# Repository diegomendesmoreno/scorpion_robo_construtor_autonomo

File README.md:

Scorpion, o Robô construtor autônomo
==============
Projeto de um Robô Construtor Autônomo, como o trabalho de conclusão de curso de Engenharia Eletrônica de 2015.

Time
--------------
- Allan Dinato Martins
- André Ferro Kopelingh
- Diego Mendes Moreno

Links
--------------
- [Blog - Scorpion, o Robô construtor autônomo](http://engenoob.blogspot.com.br/2015/06/scorpion-robo-construtor-autonomo.html)
- [YouTube - Scorpion, o Robô construtor autônomo](https://youtu.be/ymfdhoq2V6s)

Transcrição do código Arduino scorpion_robo_construtor_autonomo.ino
--------------

```c
/* Nome   : scorpion_robo_construtor_autonomo
 * Alunos : Allan Dinato Martins
 *          Andre Ferro Kopelingh
 *          Diego Mendes Moreno
 */

/* Includes */
#include <Stepper.h>
#include <Ultrasonic.h>
#include <Servo.h>

/* Pinos */
//Steppers
#define D1           22   //azul
#define D2           24   //rosa
#define D3           26   //amarelo
#define D4           28   //laranja
#define E1           30   //azul
#define E2           32   //rosa
#define E3           34   //amarelo
#define E4           36   //laranja
//Servos
#define serv_base_1  50   //servo da base direito
#define serv_base_2  52   //servo da base esquerdo
#define serv_brac_1  51   //servo do braço direito
#define serv_brac_2  53   //servo do braço esquerdo
#define serv_garra   8    //servo da garra
//Sensores Ultrasom
///Ultra 10
#define echoPin_f    48
#define trigPin_f    49
///Ultra 4
#define echoPin_fc   35
#define trigPin_fc   37
///Ultra 9
#define echoPin_d1   46
#define trigPin_d1   47
///Ultra 8
#define echoPin_d2   44
#define trigPin_d2   45
///Ultra 7
#define echoPin_e1   42
#define trigPin_e1   43
///Ultra 6
#define echoPin_e2   40
#define trigPin_e2   41
///Ultra 5
#define echoPin_t    38
#define trigPin_t    39

/* Defines */
//Constantes
#define ATRASO         2
#define OFFSET_LATERAL 0.2
#define OFFSET_AJUSTE  0.5
#define DIVISOR_ARRUM  0.04
#define CNT_MAPA_MAX   4000

/* Subrotinas */
//Sensores Ultrasom
void leitura_sensores(void);
void ultrasom(void);
void ultra_valores(void);
void limpa_media(void);
//Steppers
void frente(float passos);
void tras(int passos);
void virar_dir(int graus);
void virar_esq(int graus);
//Braço
void inicial_servos();
void garra_abre();
void garra_fecha();
void base_avanca(int angbase);
void braco_avanca(int angbase, int angmeio);
void base_retorna(int angbase);
void braco_retorna(int angbase, int angmeio);
void braco_mix(int angbase, int angmeio);
void meio_avanca(int angmeio);
void meio_retorna(int angmeio);
void anda_reto(int passos);
void vai_base(int angbase);
void vai_braco(int angbase, int angmeio);
void pega(void);
void coloca_1st(void);
void coloca_2nd(void);
void coloca_3rd(void);

/* Variáveis Globais */
//Steppers
double passos_total = 2048;       //Nº de passos p/ 1 rev.
int angulo = 90;                  //Angulo de rotacao do eixo
double numero_de_passos;          //Nº de passos
int offset = 205;
//Ultrasom
volatile unsigned int cnt = 0;
volatile int flag_ultrasom = 1;
volatile float duration;
volatile float distancia_f[9];    //distancia[0] carrega a última média de valores
volatile float distancia_fc[9];   //distancia[0] carrega a última média de valores
volatile float distancia_d1[9];   //distancia[0] carrega a última média de valores
volatile float distancia_d2[9];   //distancia[0] carrega a última média de valores
volatile float distancia_e1[9];   //distancia[0] carrega a última média de valores
volatile float distancia_e2[9];   //distancia[0] carrega a última média de valores
volatile float distancia_t[9];    //distancia[0] carrega a última média de valores
volatile int i = 1;               //index dos valores de média
//Posicoes maximas dos motores
int posgarra = 30;
int posb_zero= 0;
int posb_fim= 180;
int posm_zero= 0;
int posm_fim= 180;
//contadores
int j;
int contb=0;
int contm=0;
// inicio base
int posb_dir=98;
int posb_esq=82;
//inicio meio
int posm_dir = 112;
int posm_esq = 43;
//velocidades
int delayb_avanco=40;
int delayb_retorno=40;
int delaym_avanco=40;
int delaym_retorno=50;
//pegar
int angb[5] = {90, 80, 70, 60, 0};
int angm[5] = {160, 130, 110, 90, 70};
//so enquanto testo e atualizo todo o programa
int angb_peg[5] = {90, 80, 70, 60, 50};
int angm_peg[5] = {150, 130, 110, 90, 70};
int angmhoje, angbhoje;
int d =500;
//Máquina de Estados
int ESTADO = 0;
volatile unsigned int cnt_mapa = 0;
float dist_alvo_d[6];
float dist_alvo_e[6];
int index_percurso = 0;               //index dos valores de distância de alvo
int flag_ajuste = 1;                  //flag ajuste
float andar;
float dist_andar;
float passos_step;
float dist_arrum;
int flag_arrum;
float const_arrum;

//Definição dos steppers
Stepper stepper_dir(passos_total, D1, D3, D2, D4);
Stepper stepper_esq(passos_total, E1, E3, E2, E4);
//Definição dos servos
Servo servob_dir;
Servo servob_esq;
Servo servo_garra;
Servo servom_dir;
Servo servom_esq;

//---------------------------------------------------------------------------------

void setup()
{
  /* Sensores Ultrasom */
  pinMode(trigPin_f, OUTPUT);
  pinMode(echoPin_f, INPUT);
  pinMode(trigPin_fc, OUTPUT);
  pinMode(echoPin_fc, INPUT);
  pinMode(trigPin_d1, OUTPUT);
  pinMode(echoPin_d1, INPUT);
  pinMode(trigPin_d2, OUTPUT);
  pinMode(echoPin_d2, INPUT);
  pinMode(trigPin_e1, OUTPUT);
  pinMode(echoPin_e1, INPUT);
  pinMode(trigPin_e2, OUTPUT);
  pinMode(echoPin_e2, INPUT);
  pinMode(trigPin_t, OUTPUT);
  pinMode(echoPin_t, INPUT);
  
  /* Configuração dos Steppers */
  stepper_dir.setSpeed(10);
  stepper_esq.setSpeed(10);
  
  //Servos
  servob_dir.attach(serv_base_1);
  servob_esq.attach(serv_base_2);
  servo_garra.attach(serv_garra);
  servom_dir.attach(serv_brac_1);
  servom_esq.attach(serv_brac_2);
  
  //seta o vetor de distancias
  limpa_media();
  
  //Distâncias da parede
  dist_alvo_d[0] = 6;
  dist_alvo_d[1] = 6.5;
  dist_alvo_d[2] = 16.2;
  dist_alvo_d[3] = 6.5;
  dist_alvo_d[4] = 30;
  dist_alvo_d[5] = 6.5;
  
  dist_alvo_e[0] = 30;
  dist_alvo_e[1] = 30;
  dist_alvo_e[2] = 15.5;
  dist_alvo_e[3] = 30;
  dist_alvo_e[4] = 6.5;
  dist_alvo_e[5] = 30;
  
  inicial_servos();
}

void loop()
{
  ++cnt;
  
  if(cnt >= ATRASO)
  {
    cnt = 0;
    leitura_sensores();
  }
  
  //Máquina de Estados
  switch(ESTADO)
  {
    case 0 :
      //localizar-se
      if(cnt_mapa < CNT_MAPA_MAX)
      {
        ++cnt_mapa;
      }
      else
      {
        vai_braco(130, 10);
        
        if(distancia_f[0] > 10)
        {
          ESTADO = 1;
        }
      }
      break;
      
    case 1 :
      //E8
      if(distancia_f[0] <= 10)
      {
        cnt_mapa = 0;
        ESTADO = 8;
        break;
      }
      
      if(index_percurso != 4)
      {
        //E2
        if(distancia_d1[0] > (distancia_d2[0] + OFFSET_LATERAL))
        {
          ESTADO = 2;
          break;
        }
        
        //E3
        if(distancia_d1[0] < (distancia_d2[0] - OFFSET_LATERAL))
        {
          ESTADO = 3;
          break;
        }
      }
      else if(index_percurso == 4)
      {
        //E2
        if(distancia_e1[0] < (distancia_e2[0] - OFFSET_LATERAL))
        {
          ESTADO = 2;
          break;
        }
        
        //E3
        if(distancia_e1[0] > (distancia_e2[0] + OFFSET_LATERAL))
        {
          ESTADO = 3;
          break;
        }
      }
      
      if(index_percurso != 4)
      {
        //E4 e E6
        if(distancia_d1[0] > (dist_alvo_d[index_percurso] + OFFSET_LATERAL))
        {
          if(flag_ajuste == 1)
          {
            ESTADO = 4;
            flag_ajuste = 0;
          }
          else
          {
            ESTADO = 6;
          }
          break;
        }
        
        //E5 e E7
        if(distancia_d1[0] < (dist_alvo_d[index_percurso] - OFFSET_LATERAL))
        {
          if(flag_ajuste == 1)
          {
            ESTADO = 5;
            flag_ajuste = 0;
          }
          else
          {
            ESTADO = 7;
          }
          break;
        }
      }
      
      if(index_percurso == 4)
      {
        //E4
        if(distancia_e1[0] < (dist_alvo_e[index_percurso] - OFFSET_LATERAL))
        {
          ESTADO = 6;
          break;
        }
      
        //E5
        if(distancia_e1[0] > (dist_alvo_e[index_percurso] + OFFSET_LATERAL))
        {
          if(flag_ajuste == 1)
          {
            ESTADO = 5;
            flag_ajuste = 0;
          }
          else
          {
            ESTADO = 7;
          }
          break;
        }
      }
      
      frente(1);
      break;
      
    case 2 :
      stepper_esq.step(-1);
      ESTADO = 1;
      break;
      
    case 3 :
      stepper_dir.step(1);
      ESTADO = 1;
      break;
    
    case 4 :
      //cálculo
      if(distancia_d1[0] > dist_alvo_d[index_percurso])
      {
        andar = distancia_d1[0] - dist_alvo_d[index_percurso];
        dist_andar = andar/0.707;
        passos_step = (dist_andar/20.0)*2048.0;
        
        //andar
        virar_dir(45);
        frente(passos_step);
        virar_esq(45);
      }
      else if(distancia_d1[0] < dist_alvo_d[index_percurso])
      {
        andar = dist_alvo_d[index_percurso] - distancia_d1[0];
        dist_andar = andar/0.707;
        passos_step = (dist_andar/20.0)*2048.0;
        
        //andar
        virar_esq(45);
        frente(passos_step);
        virar_dir(45);
      }
      ESTADO = 1;
      break;
    
    case 5 :
      //cálculo
      if(distancia_e1[0] > dist_alvo_e[index_percurso])
      {
        andar = distancia_e1[0] - dist_alvo_e[index_percurso];
        dist_andar = andar/0.707;
        passos_step = (dist_andar/20.0)*2048;
        
        //andar
        virar_esq(45);
        frente(passos_step);
        virar_dir(45);
      }
      ESTADO = 1;
      break;
    
    case 6 :
      stepper_esq.step(-5);
      frente(5);
      ESTADO = 1;
      break;
    
    case 7 :
      stepper_dir.step(5);
      frente(5);
      ESTADO = 1;
      break;
    
    case 8 :
      //localizar-se
      if(cnt_mapa < CNT_MAPA_MAX)
      {
        ++cnt_mapa;
      }
      else
      {
        if(index_percurso != 4)
        {
          if(distancia_d1[0] > (distancia_d2[0] + OFFSET_AJUSTE))
          {
            dist_arrum = distancia_d1[0] - distancia_d2[0];
            flag_arrum = 0;
            const_arrum = dist_arrum/DIVISOR_ARRUM;
          }
          else if(distancia_d1[0] < (distancia_d2[0] - OFFSET_AJUSTE))
          {
            dist_arrum = distancia_d2[0] - distancia_d1[0];
            flag_arrum = 1;
            const_arrum = dist_arrum/DIVISOR_ARRUM;
          }
        }
        else if(index_percurso == 4)
        {
          if(distancia_e1[0] > (distancia_e2[0] + OFFSET_AJUSTE))
          {
            dist_arrum = distancia_e1[0] - distancia_e2[0];
            flag_arrum = 2;
            const_arrum = dist_arrum/DIVISOR_ARRUM;
          }
          else if(distancia_e1[0] < (distancia_e2[0] - OFFSET_AJUSTE))
          {
            dist_arrum = distancia_e2[0] - distancia_e1[0];
            flag_arrum = 3;
            const_arrum = dist_arrum/DIVISOR_ARRUM;
          }
        }
        ESTADO = 9;
      }
      break;
    
    case 9 :
      while(const_arrum > 0)
      {
        if(flag_arrum == 0 || flag_arrum == 2)
        {
          stepper_dir.step(-1);
          stepper_esq.step(-1);
        }
        else if(flag_arrum == 1 || flag_arrum == 3)
        {
          stepper_dir.step(1);
          stepper_esq.step(1);
        }
        --const_arrum;
      }
      ESTADO = 10;
      break;
    
    case 10 :
      if(index_percurso == 0)
      {
        pega();
        
        tras(100);
        virar_esq(90);
        virar_esq(90);
        
        ++index_percurso;
        flag_ajuste = 1;
        cnt_mapa = 0;
        ESTADO = 0;
      }
      else if(index_percurso == 1)
      {
        coloca_1st();
        
        tras(200);
        virar_esq(90);
        virar_esq(90);
        
        ++index_percurso;
        flag_ajuste = 1;
        cnt_mapa = 0;
        ESTADO = 0;
      }
      else if(index_percurso == 2)
      {
        pega();
        
        tras(200);
        virar_esq(90);
        virar_esq(90);
        
        ++index_percurso;
        flag_ajuste = 1;
        cnt_mapa = 0;
        ESTADO = 0;
      }
      else if(index_percurso == 3)
      {
        coloca_2nd();
        
        tras(200);
        virar_esq(90);
        virar_esq(90);
        
        ++index_percurso;
        flag_ajuste = 1;
        cnt_mapa = 0;
        ESTADO = 0;
      }
      else if(index_percurso == 4)
      {
        pega();
        
        tras(100);
        virar_dir(90);
        virar_dir(90);
        
        ++index_percurso;
        flag_ajuste = 1;
        cnt_mapa = 0;
        ESTADO = 0;
      }
      else if(index_percurso == 5)
      {
        coloca_3rd();
        
        tras(300);
        
        //Posição escorpião
        vai_braco(130, 10);
        delay(d);
        
        garra_fecha();
        garra_abre();
        
        delay(2000);
        
        virar_esq(90);
        virar_esq(90);
        
        delay(5000);
        
        vai_braco(100, 110);
        
        while(1);
      }
      break;
  }
}

//---------------------------------------------------------------------------------

/* Subrotina : leitura_sensores
 */
void leitura_sensores(void)
{
  if(flag_ultrasom <= 5)
  {
    ultrasom();
    ++flag_ultrasom;
  }
  else
  {
    if(i <= 8)  //quantidade de medições para a média
    {
      ++i;
    }
    else
    {
      i = 1;
    }
    flag_ultrasom = 1;
    ultrasom();
  }
  
  ultra_valores();
}

/* Subrotina : ultrasom
 */
void ultrasom(void)
{
  switch(flag_ultrasom)
  {
    case 1 :
      //Ultrasom frente
      digitalWrite(trigPin_f, LOW);
      delayMicroseconds(2);
      digitalWrite(trigPin_f, HIGH);
      delayMicroseconds(10);
      digitalWrite(trigPin_f, LOW);
      duration = pulseIn(echoPin_f, HIGH);
      distancia_f[i] = (340*duration/2)/10000;
      break;
    case 2 :
      //Ultrasom dir1
      digitalWrite(trigPin_d1, LOW);
      delayMicroseconds(2);
      digitalWrite(trigPin_d1, HIGH);
      delayMicroseconds(10);
      digitalWrite(trigPin_d1, LOW);
      duration = pulseIn(echoPin_d1, HIGH);
      distancia_d1[i] = (340*duration/2)/10000;
      break;
    case 3 :
      //Ultrasom dir2
      digitalWrite(trigPin_d2, LOW);
      delayMicroseconds(2);
      digitalWrite(trigPin_d2, HIGH);
      delayMicroseconds(10);
      digitalWrite(trigPin_d2, LOW);
      duration = pulseIn(echoPin_d2, HIGH);
      distancia_d2[i] = (340*duration/2)/10000;
      break;
    case 4 :
      //Ultrasom esq1
      digitalWrite(trigPin_e1, LOW);
      delayMicroseconds(2);
      digitalWrite(trigPin_e1, HIGH);
      delayMicroseconds(10);
      digitalWrite(trigPin_e1, LOW);
      duration = pulseIn(echoPin_e1, HIGH);
      distancia_e1[i] = (340*duration/2)/10000;
      break;
    case 5 :
      //Ultrasom esq2
      digitalWrite(trigPin_e2, LOW);
      delayMicroseconds(2);
      digitalWrite(trigPin_e2, HIGH);
      delayMicroseconds(10);
      digitalWrite(trigPin_e2, LOW);
      duration = pulseIn(echoPin_e2, HIGH);
      distancia_e2[i] = (340*duration/2)/10000;
      break;
  }
}

/* Subrotina : ultra_valores
 */
void ultra_valores(void)
{
  int j = 1;
  
  //Ultrasom frente
  for(j = 1;j <= 4; j++)
  {
    if(distancia_f[j] > 2 && distancia_f[j] < 100)
    {
      distancia_f[0] = (distancia_f[1]/8) + (distancia_f[2]/8) + (distancia_f[3]/8) + (distancia_f[4]/8) + (distancia_f[5]/8) + (distancia_f[6]/8) + (distancia_f[7]/8) + (distancia_f[8]/8);
    }
    else
    {
      distancia_f[j] = distancia_f[0];  //se o valor estiver fora, igualar a média
    }
  }
  
  //Ultrasom dir1
  for(j = 1;j <= 4; j++)
  {
    if(distancia_d1[j] > 2 && distancia_d1[j] < 100)
    {
      distancia_d1[0] = (distancia_d1[1]/8) + (distancia_d1[2]/8) + (distancia_d1[3]/8) + (distancia_d1[4]/8) + (distancia_d1[5]/8) + (distancia_d1[6]/8) + (distancia_d1[7]/8) + (distancia_d1[8]/8);
    }
    else
    {
      distancia_d1[j] = distancia_d1[0];  //se o valor estiver fora, igualar a média
    }
  }
  
  //Ultrasom dir2
  for(j = 1;j <= 4; j++)
  {
    if(distancia_d2[j] > 2 && distancia_d2[j] < 100)
    {
      distancia_d2[0] = (distancia_d2[1]/8) + (distancia_d2[2]/8) + (distancia_d2[3]/8) + (distancia_d2[4]/8) + (distancia_d2[5]/8) + (distancia_d2[6]/8) + (distancia_d2[7]/8) + (distancia_d2[8]/8);
    }
    else
    {
      distancia_d2[j] = distancia_d2[0];  //se o valor estiver fora, igualar a média
    }
  }
  
  //Ultrasom esq1
  for(j = 1;j <= 4; j++)
  {
    if(distancia_e1[j] > 2 && distancia_e1[j] < 100)
    {
      distancia_e1[0] = (distancia_e1[1]/8) + (distancia_e1[2]/8) + (distancia_e1[3]/8) + (distancia_e1[4]/8) + (distancia_e1[5]/8) + (distancia_e1[6]/8) + (distancia_e1[7]/8) + (distancia_e1[8]/8);
    }
    else
    {
      distancia_e1[j] = distancia_e1[0];  //se o valor estiver fora, igualar a média
    }
  }
  
  //Ultrasom esq2
  for(j = 1;j <= 4; j++)
  {
    if(distancia_e2[j] > 2 && distancia_e2[j] < 100)
    {
      distancia_e2[0] = (distancia_e2[1]/8) + (distancia_e2[2]/8) + (distancia_e2[3]/8) + (distancia_e2[4]/8) + (distancia_e2[5]/8) + (distancia_e2[6]/8) + (distancia_e2[7]/8) + (distancia_e2[8]/8);
    }
    else
    {
      distancia_e2[j] = distancia_e2[0];  //se o valor estiver fora, igualar a média
    }
  }
}

/* Subrotina : limpa_media
 */
void limpa_media(void)
{
  //frente
  distancia_f[0] = 11;
  distancia_f[1] = 11;
  distancia_f[2] = 11;
  distancia_f[3] = 11;
  distancia_f[4] = 11;
  distancia_f[5] = 11;
  distancia_f[6] = 11;
  distancia_f[7] = 11;
  distancia_f[8] = 11;
}

/* Subrotina : frente
 */
void frente(float passos)
{
  int i = 0;
  
  for(i = 0;i < passos;i++)
  {
    stepper_dir.step(1);
    stepper_esq.step(-1);
  }
}

/* Subrotina : tras
 */
void tras(int passos)
{
  int i = 0;
  
  for(i = 0;i < passos;i++)
  {
    stepper_dir.step(-1);
    stepper_esq.step(1);
  }
}

/* Subrotina : virar_dir
 */
void virar_dir(int graus)
{
  int i = 0;
  
  //Quantidade de passos, baseado no angulo determinado
  numero_de_passos = offset + 2*(graus / (360 / passos_total));
  
  for(i = 0;i < numero_de_passos;i++)
  {
    stepper_dir.step(-1);
    stepper_esq.step(-1);
  }
}

/* Subrotina : virar_esq
 */
void virar_esq(int graus)
{
  int i = 0;
  
  //Quantidade de passos, baseado no angulo determinado
  numero_de_passos = offset + 2*(graus / (360 / passos_total));
  
  for(i = 0;i < numero_de_passos;i++)
  {
    stepper_dir.step(1);
    stepper_esq.step(1);
  }
}

//-------------------------------------------------------------------------

/* Subrotina : inicial_servos
 */
 void inicial_servos()
 {
   servob_dir.write(posb_dir);
   servob_esq.write(posb_esq);
   servom_esq.write(posm_esq);
   servom_dir.write(posm_dir);
   servo_garra.write(posgarra); 
  
}

/* Subrotina : garra_abre
 */
void garra_abre()
{
  while(posgarra < 160)
  {
    servo_garra.write(posgarra); 
    ++posgarra;
    delay(10);
  }
  
}

/* Subrotina : garra_fecha
 */
void garra_fecha()
{
  while(posgarra > 40)
  {
    servo_garra.write(posgarra);
    --posgarra;
    delay(10);  
  } 
}

/* Subrotina : base_avanca
 */
void base_avanca(int angbase)
{
 while(posb_dir > angbase)
  {
    servob_dir.write(posb_dir);
    servob_esq.write(posb_esq);
    --posb_dir;
    ++posb_esq;
    delay(delayb_avanco);
  }
}

/* Subrotina : braco_avanca
 */
void braco_avanca(int angbase, int angmeio)
{
  while(posb_dir > angbase)
  {
    servob_dir.write(posb_dir);
    servob_esq.write(posb_esq);
    
    --posb_dir;
    ++posb_esq;
    delay(delaym_avanco);
    
    if(posm_dir< angmeio)
    {
      servom_esq.write(posm_esq);
      servom_dir.write(posm_dir); 
      ++posm_dir;
      --posm_esq;
    }
  }
  
  while(posm_dir < angmeio)
  {
    servom_esq.write(posm_esq);
    servom_dir.write(posm_dir); 
    ++posm_dir;
    --posm_esq;
    delay(delaym_avanco);
  }
  
}

/* Subrotina : base_retorna
 */
void base_retorna(int angbase)
{
  while(posb_dir < angbase)
  {
    servob_dir.write(posb_dir);
    servob_esq.write(posb_esq);
    ++posb_dir;
    --posb_esq;
    delay(delayb_retorno);
  }
  
}

/* Subrotina : braco_retorna
 */
void braco_retorna(int angbase, int angmeio)
{
  while(posb_dir < angbase)
  {
    servob_dir.write(posb_dir);
    servob_esq.write(posb_esq);
    ++posb_dir;
    --posb_esq;
    delay(delaym_retorno);
    
    if(posm_dir > angmeio)
    {
      servom_esq.write(posm_esq);
      servom_dir.write(posm_dir);
      --posm_dir;
      ++posm_esq;
    }
  
  }
  
  while(posm_dir > angmeio)
  {
    servom_esq.write(posm_esq);
    servom_dir.write(posm_dir);
    --posm_dir;
    ++posm_esq;
    delay(delaym_retorno);  
  }
  
}

/* Subrotina : braco_mix
 */
void braco_mix(int angbase, int angmeio)
{
  while(posb_dir > angbase)
  {
    servob_dir.write(posb_dir);
    servob_esq.write(posb_esq);
    
    --posb_dir;
    ++posb_esq;
    delay(delaym_avanco);
    
    if(posm_dir< angmeio)
    {
      servom_esq.write(posm_esq);
      servom_dir.write(posm_dir); 
      ++posm_dir;
      --posm_esq;
    }
    if(posm_dir > angmeio)
    {
      servom_esq.write(posm_esq);
      servom_dir.write(posm_dir);
      --posm_dir;
      ++posm_esq;
    } 
  }
  
  while(posb_dir < angbase)
  {
    servob_dir.write(posb_dir);
    servob_esq.write(posb_esq);
    ++posb_dir;
    --posb_esq;
    delay(delaym_retorno);
    
    if(posm_dir > angmeio)
    {
      servom_esq.write(posm_esq);
      servom_dir.write(posm_dir);
      --posm_dir;
      ++posm_esq;
    }
    if( posm_dir < angmeio)
    {
      servom_esq.write(posm_esq);
      servom_dir.write(posm_dir); 
      ++posm_dir;
      --posm_esq;
    }
  }
  
  //completa movimento meio
  while(posm_dir > angmeio)
  {
    servom_esq.write(posm_esq);
    servom_dir.write(posm_dir);
    --posm_dir;
    ++posm_esq;
    delay(delaym_retorno);  
  }
  //completa movimento meio
  while(posm_dir < angmeio)
  {
    servom_esq.write(posm_esq);
    servom_dir.write(posm_dir); 
    ++posm_dir;
    --posm_esq;
    delay(delaym_avanco);
  }
  
}
  
/* Subrotina : meio_avanca
 */
void meio_avanca(int angmeio)
{
  while(posm_dir < angmeio)
  {
    servom_esq.write(posm_esq);
    servom_dir.write(posm_dir); 
    ++posm_dir;
    --posm_esq;
    delay(delaym_avanco);
  }
}

/* Subrotina : meio_retorna
 */
void meio_retorna(int angmeio)
{
  while(posm_dir > angmeio)
  {
    servom_esq.write(posm_esq);
    servom_dir.write(posm_dir);
    --posm_dir;
    ++posm_esq;
    delay(delaym_retorno);  
  }
  
}

/* Subrotina : anda_reto
 */
void anda_reto(int passos)
{
  int angbase = posb_dir;
  int angmeio = posm_dir;
  j=passos;
  while(j>0){
  
  angbase= angbase-1;
  angmeio= angmeio-2;  
    
  base_avanca(angbase);
  meio_retorna(angmeio);
  delay(10);
 
  j--;
    }
}

/* Subrotina : vai_base
 * Descrição : 
 */
void vai_base(int angbase)
{
  if(angbase < posb_dir){
    base_avanca(angbase);
  }
  if(angbase > posb_dir){
    base_retorna(angbase);}  
}

/* Subrotina : vai_braco
 */
void vai_braco(int angbase, int angmeio)
{
  if(posb_dir > angbase && posm_dir < angmeio)
  braco_avanca(angbase, angmeio);
  
 if( posb_dir < angbase && posm_dir > angmeio)
   braco_retorna(angbase,angmeio);
 
 else
   braco_mix(angbase, angmeio);
}

/* Subrotina : pega
 */
void pega(void)
{
  delay(100);
  
  garra_abre();
  vai_braco(45, 14);
  delay(d);
  
  if(index_percurso == 0)
  {
    frente(300);
  }
  else if(index_percurso == 3)
  {
    frente(220);
  }
  else
  {
    frente(270);
  }  
  
  vai_braco(45, 14);
  delay(d);
  garra_fecha();
  vai_braco(50, 14);
  delay(d);
  tras(400);
  vai_braco(130, 10);
  delay(d);
}

/* Subrotina : coloca_1st
 */
void coloca_1st(void)
{
  //Anda até o bloquinho
  delay(200);
  tras(1000);
  delay(100);
  
  vai_braco(44, 14);
  delay(d);
  garra_abre();
  vai_braco(130, 10);
  delay(d);
}

/* Subrotina : coloca_2nd
 */
void coloca_2nd(void)
{
  //Anda até o bloquinho
  delay(200);
  frente(200);
  delay(100);
  
  vai_braco(55, 10);
  delay(d);
  garra_abre();
  vai_braco(130, 10);
  delay(d);
}

/* Subrotina : coloca_3rd
 */
void coloca_3rd(void)
{
  //Anda até o bloquinho
  delay(200);
  frente(220);
  delay(100);
  
  vai_braco(66, 6);
  delay(d);
  garra_abre();
  vai_braco(90, 50);
  delay(d);
}
```

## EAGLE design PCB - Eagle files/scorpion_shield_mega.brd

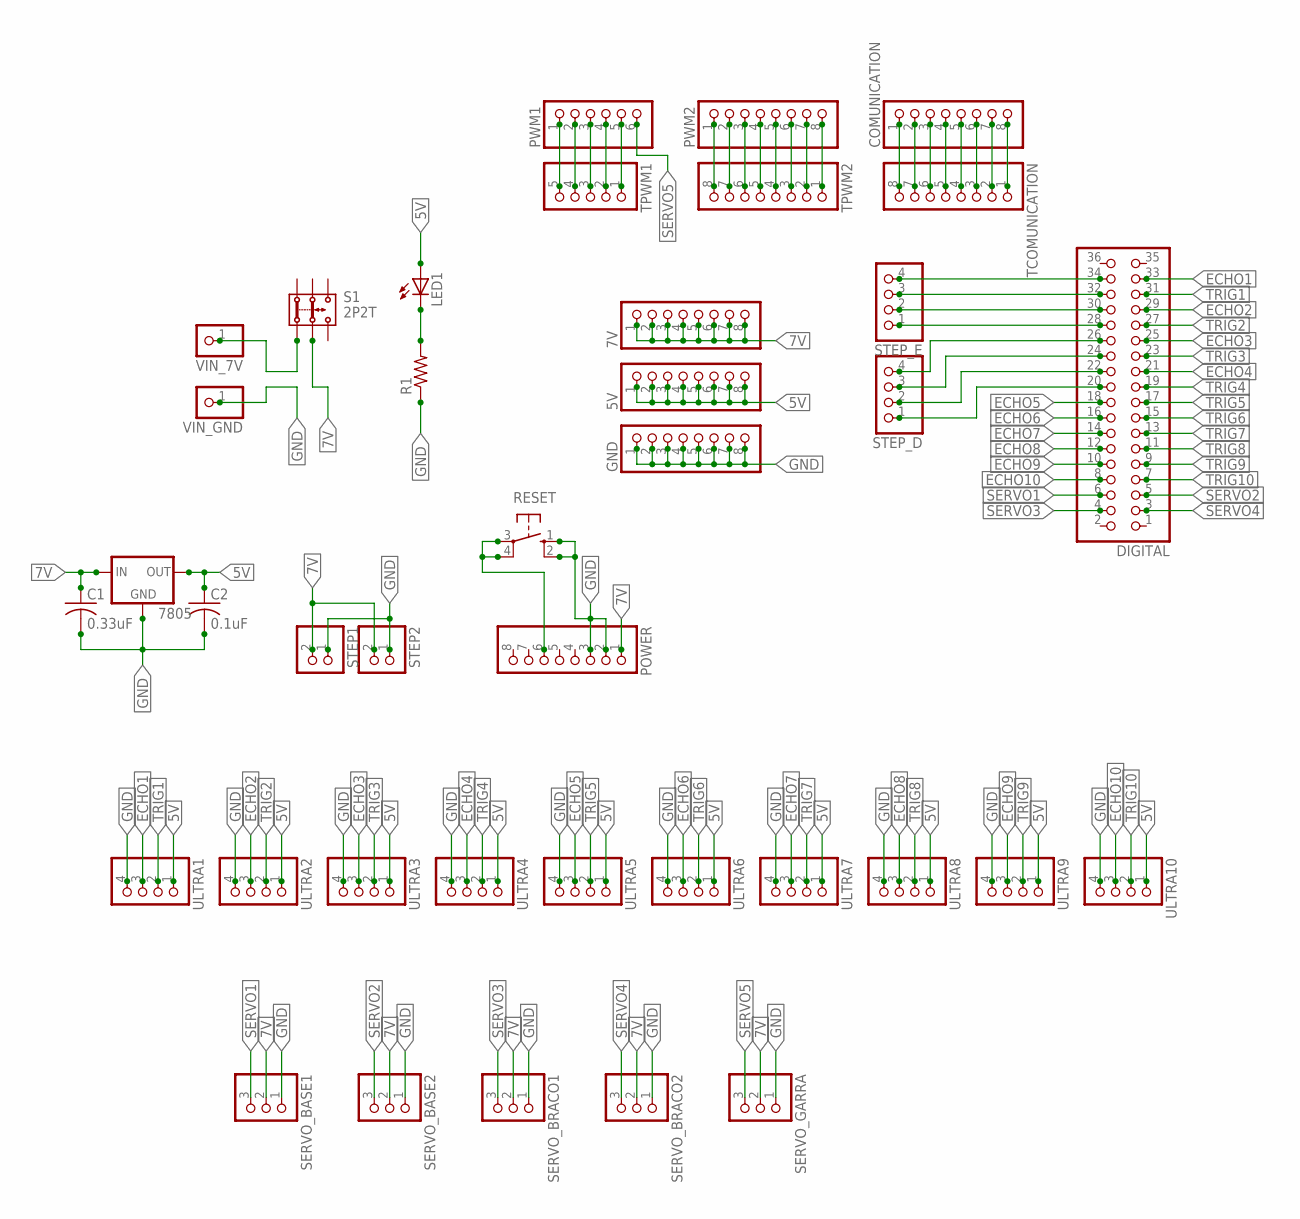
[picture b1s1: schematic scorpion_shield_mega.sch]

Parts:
5V, 7V: PINHD-1X8; 1X08
7805: 78XXS
C1: 0.33uF; C050-025X075
C2: 0.1uF; C050-025X075
COMUNICATION: PINHD-1X8; 1X08
DIGITAL: PINHD-2X18; 2X18
GND: PINHD-1X8; 1X08
LED1: LED5MM
POWER: PINHD-1X8; 1X08
PWM1: PINHD-1X6; 1X06
PWM2: PINHD-1X8; 1X08
R1: R-US_0204/7; 0204/7
RESET: 10-XX; B3F-10XX
S1: 2P2T
SERVO_BASE1, SERVO_BASE2: PINHD-1X3; 1X03
SERVO_BRACO1, SERVO_BRACO2: PINHD-1X3; 1X03
SERVO_GARRA: PINHD-1X3; 1X03
STEP1, STEP2: PINHD-1X2; 1X02
STEP_D: PINHD-1X4; 1X04
STEP_E: PINHD-1X4; 1X04
TCOMUNICATION: PINHD-1X8; 1X08
TPWM1: PINHD-1X5; 1X05
TPWM2: PINHD-1X8; 1X08
ULTRA1, ULTRA2, ULTRA3, ULTRA4, ULTRA5, ULTRA6, ULTRA7, ULTRA8, ULTRA9, ULTRA10: PINHD-1X4; 1X04
VIN_7V: PINHD-1X1; 1X01
VIN_GND: PINHD-1X1; 1X01

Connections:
5V: 5V.1, 5V.2, 5V.3, 5V.4, 5V.5, 5V.6, 5V.7, 5V.8, 7805.OUT, C2.1, LED1.A, ULTRA1.1, ULTRA2.1, ULTRA3.1, ULTRA4.1, ULTRA5.1, ULTRA6.1, ULTRA7.1, ULTRA8.1, ULTRA9.1, ULTRA10.1
7V: 7V.1, 7V.2, 7V.3, 7V.4, 7V.5, 7V.6, 7V.7, 7V.8, 7805.IN, C1.1, POWER.1, S1.2.2, SERVO_BASE1.2, SERVO_BASE2.2, SERVO_BRACO1.2, SERVO_BRACO2.2, SERVO_GARRA.2, STEP1.2, STEP2.2
ECHO1: DIGITAL.33, ULTRA1.3
ECHO2: DIGITAL.29, ULTRA2.3
ECHO3: DIGITAL.25, ULTRA3.3
ECHO4: DIGITAL.21, ULTRA4.3
ECHO5: DIGITAL.18, ULTRA5.3
ECHO6: DIGITAL.16, ULTRA6.3
ECHO7: DIGITAL.14, ULTRA7.3
ECHO8: DIGITAL.12, ULTRA8.3
ECHO9: DIGITAL.10, ULTRA9.3
ECHO10: DIGITAL.8, ULTRA10.3
GND: 7805.GND, C1.2, C2.2, GND.1, GND.2, GND.3, GND.4, GND.5, GND.6, GND.7, GND.8, POWER.2, POWER.3, R1.1, RESET.1 (S), RESET.2 (S1), SERVO_BASE1.1, SERVO_BASE2.1, SERVO_BRACO1.1, SERVO_BRACO2.1, SERVO_GARRA.1, STEP1.1, STEP2.1, ULTRA1.4, ULTRA2.4, ULTRA3.4, ULTRA4.4, ULTRA5.4, ULTRA6.4, ULTRA7.4, ULTRA8.4, ULTRA9.4, ULTRA10.4, VIN_GND.1
unnamed: DIGITAL.34, STEP_E.4
unnamed: POWER.6, RESET.3, RESET.4 (P1)
unnamed: DIGITAL.32, STEP_E.3
unnamed: DIGITAL.30, STEP_E.2
unnamed: DIGITAL.28, STEP_E.1
unnamed: DIGITAL.26, STEP_D.4
unnamed: DIGITAL.24, STEP_D.3
unnamed: DIGITAL.22, STEP_D.2
unnamed: DIGITAL.20, STEP_D.1
unnamed: S1.1.2, VIN_7V.1
unnamed: LED1.K (C), R1.2
unnamed: PWM2.1, TPWM2.8
unnamed: PWM2.2, TPWM2.7
unnamed: PWM2.3, TPWM2.6
unnamed: PWM2.4, TPWM2.5
unnamed: PWM2.5, TPWM2.4
unnamed: PWM2.6, TPWM2.3
unnamed: PWM2.7, TPWM2.2
unnamed: PWM2.8, TPWM2.1
unnamed: COMUNICATION.1, TCOMUNICATION.8
unnamed: COMUNICATION.2, TCOMUNICATION.7
unnamed: COMUNICATION.3, TCOMUNICATION.6
unnamed: COMUNICATION.4, TCOMUNICATION.5
unnamed: COMUNICATION.5, TCOMUNICATION.4
unnamed: COMUNICATION.6, TCOMUNICATION.3
unnamed: COMUNICATION.7, TCOMUNICATION.2
unnamed: COMUNICATION.8, TCOMUNICATION.1
unnamed: PWM1.1, TPWM1.5
unnamed: PWM1.2, TPWM1.4
unnamed: PWM1.3, TPWM1.3
unnamed: PWM1.4, TPWM1.2
unnamed: PWM1.5, TPWM1.1
SERVO1: DIGITAL.6, SERVO_BASE1.3
SERVO2: DIGITAL.5, SERVO_BASE2.3
SERVO3: DIGITAL.4, SERVO_BRACO1.3
SERVO4: DIGITAL.3, SERVO_BRACO2.3
SERVO5: PWM1.6, SERVO_GARRA.3
TRIG1: DIGITAL.31, ULTRA1.2
TRIG2: DIGITAL.27, ULTRA2.2
TRIG3: DIGITAL.23, ULTRA3.2
TRIG4: DIGITAL.19, ULTRA4.2
TRIG5: DIGITAL.17, ULTRA5.2
TRIG6: DIGITAL.15, ULTRA6.2
TRIG7: DIGITAL.13, ULTRA7.2
TRIG8: DIGITAL.11, ULTRA8.2
TRIG9: DIGITAL.9, ULTRA9.2
TRIG10: DIGITAL.7, ULTRA10.2

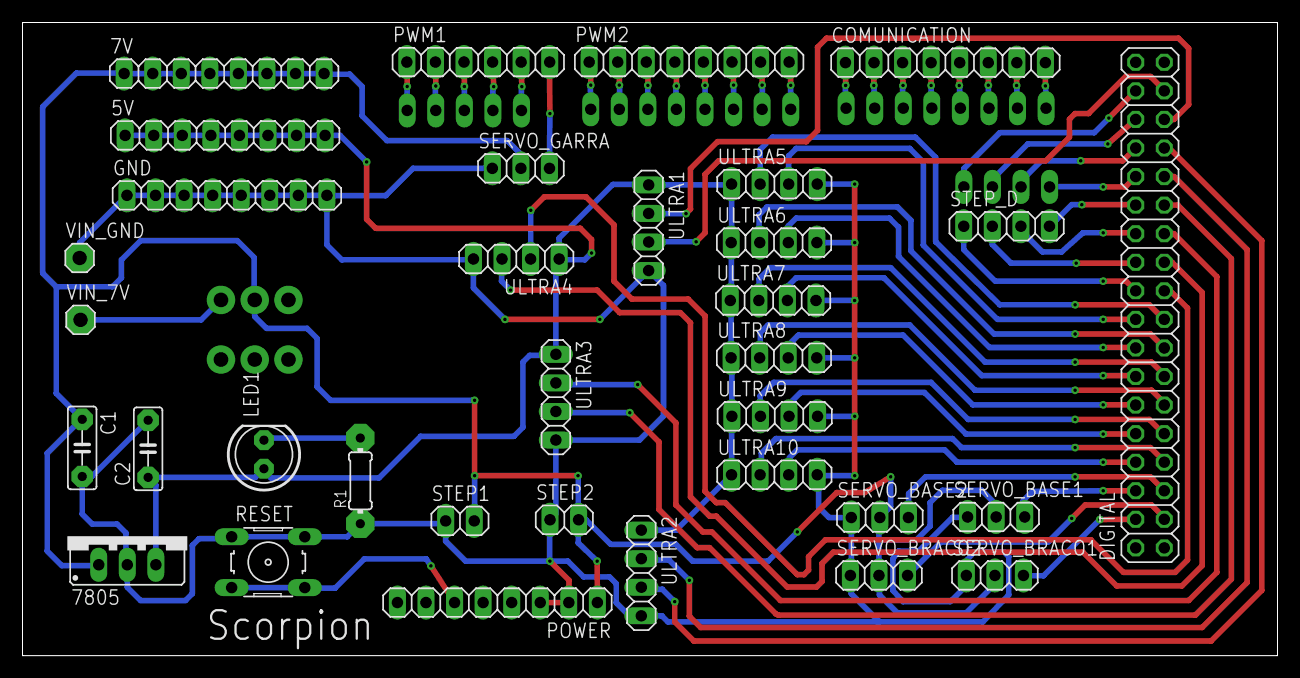
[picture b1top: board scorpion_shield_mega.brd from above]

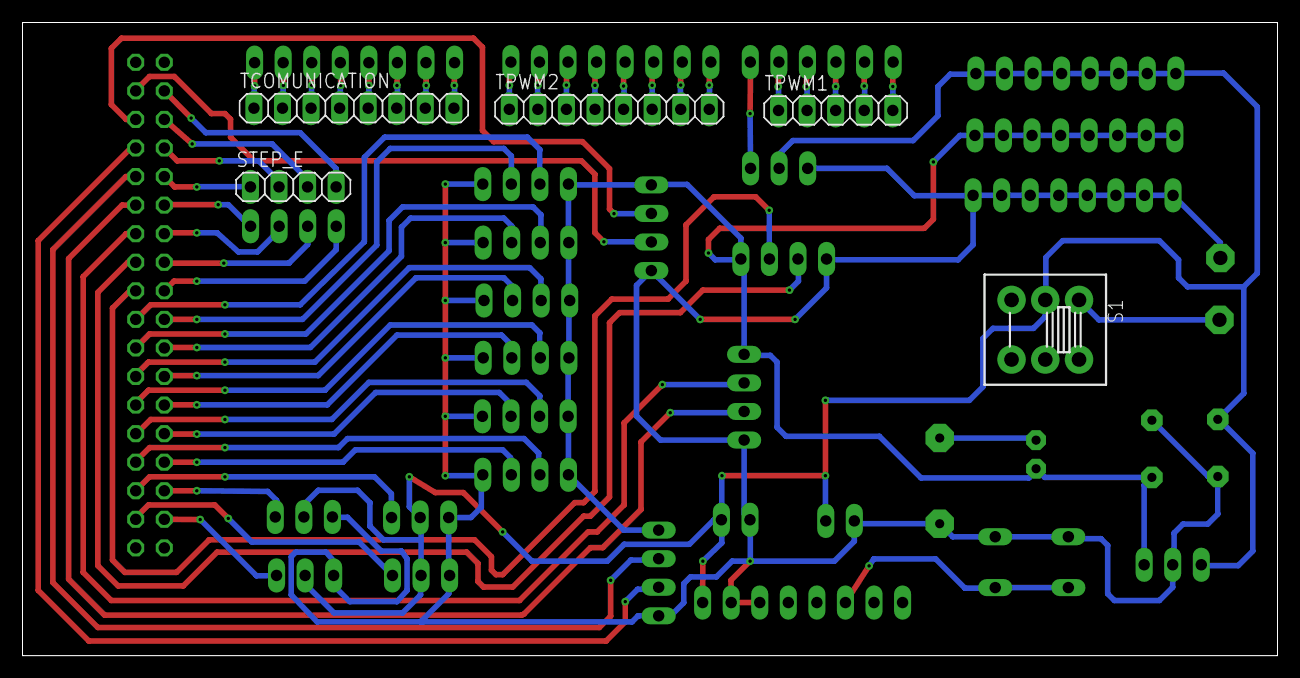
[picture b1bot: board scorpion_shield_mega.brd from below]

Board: 2 copper layers, 111.6 x 56.3 mm, 39 parts (5 on the bottom side), 60 nets.
